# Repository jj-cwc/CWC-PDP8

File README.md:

# CWC-PDP8
PDP-8 implementation on an FPGA

For more information, please see:
- [Cold War Computing website](http://coldwarcomputing.com)
- [PDP-8 Maintenance Manual, Vol. 1](http://vandermark.ch/pdp8/uploads/PDP8/PDP8.Manuals/DEC-8E-HR1C-D.pdf)
- [PDP-8 Maintenance Manual, Vol. 2](http://vandermark.ch/pdp8/uploads/PDP8/PDP8.Manuals/DEC-8E-HR2C-D.pdf)
- [PDP-8 Maintenance Manual, Vol. 3](http://vandermark.ch/pdp8/uploads/PDP8/PDP8.Manuals/DEC-8E-HMM3-D.pdf)

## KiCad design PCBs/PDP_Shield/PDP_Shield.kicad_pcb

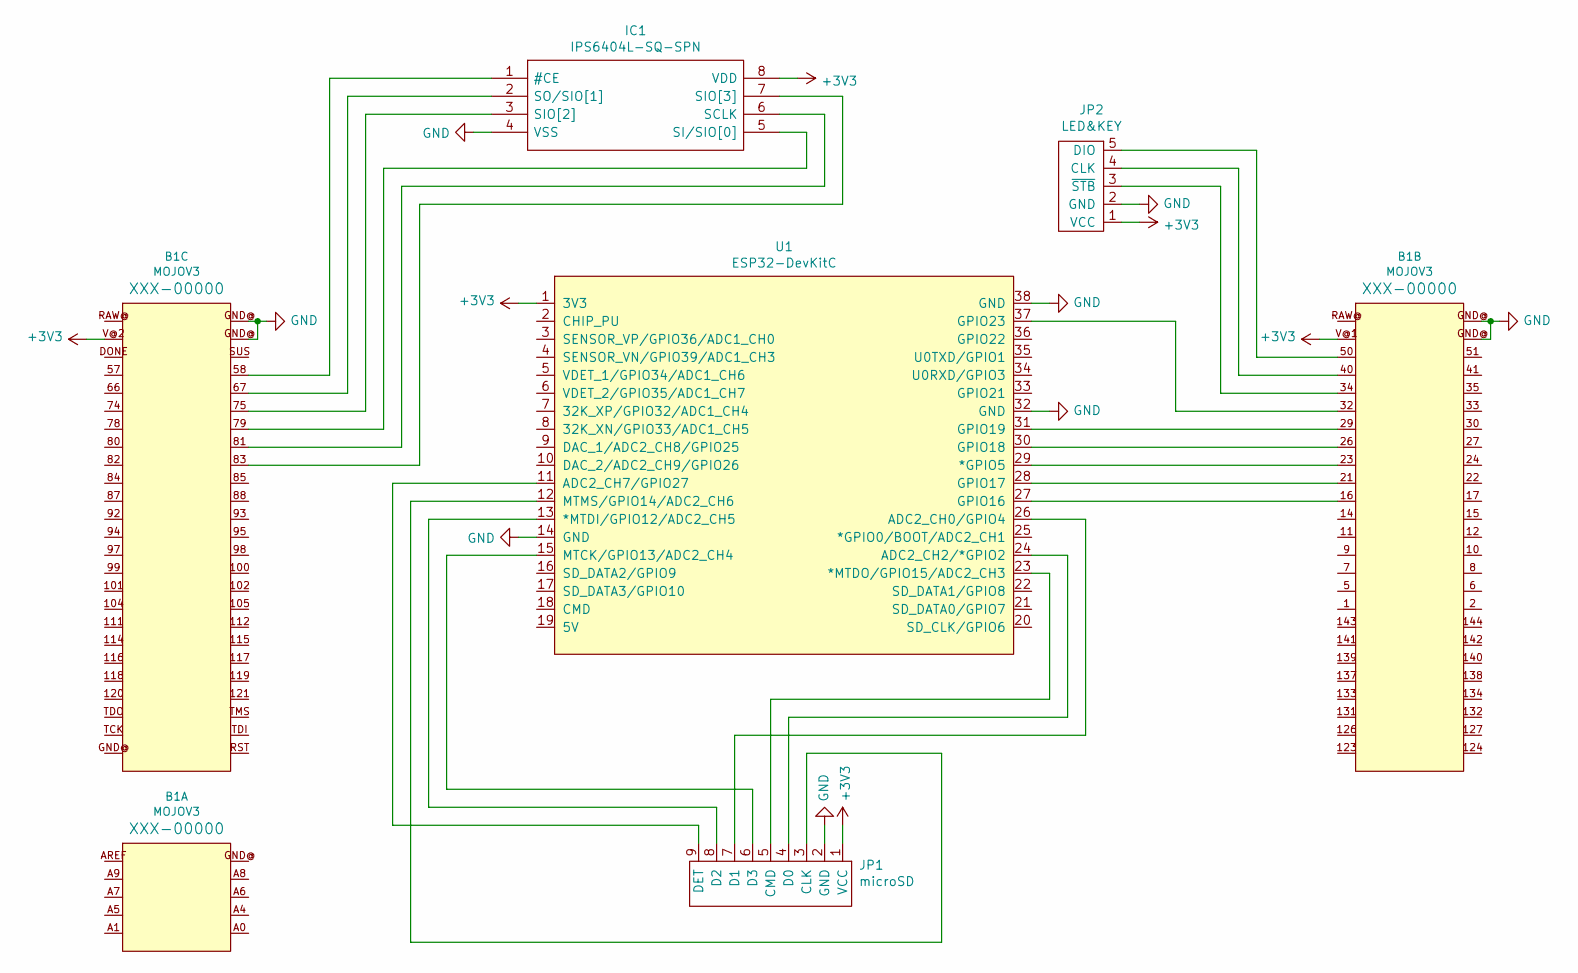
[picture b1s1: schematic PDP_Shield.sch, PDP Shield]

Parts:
B1: MOJOV3; MOJO_V3
IC1: IPS6404L-SQ-SPN; SOIC127P600X175-8N; Manufacturer_Part_Number IPS6404L-SQ-SPN
JP1: microSD; SDIO
JP2: LED&KEY
U1: ESP32-DevKitC

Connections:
+3V3: B1.V@1 (+V), B1.V@2 (+V), IC1.8 (VDD), JP1.1 (VCC), JP2.1 (VCC), U1.1 (3V3)
GND: B1.GND@ (GND), IC1.4 (VSS), JP1.2 (GND), JP2.2 (GND), U1.14 (GND), U1.32 (GND), U1.38 (GND)
unnamed: B1.16, U1.27 (GPIO16)
unnamed: B1.21, U1.28 (GPIO17)
unnamed: B1.23, U1.29 (*GPIO5)
unnamed: B1.26, U1.30 (GPIO18)
unnamed: B1.29, U1.31 (GPIO19)
unnamed: B1.32, U1.37 (GPIO23)
unnamed: B1.34, JP2.3 (~STB)
unnamed: B1.40, JP2.4 (CLK)
unnamed: B1.50, JP2.5 (DIO)
unnamed: B1.58, IC1.1 (#CE)
unnamed: B1.67, IC1.2 (SO/SIO[1])
unnamed: B1.75, IC1.3 (SIO[2])
unnamed: B1.79, IC1.5 (SI/SIO[0])
unnamed: B1.81, IC1.6 (SCLK)
unnamed: B1.83, IC1.7 (SIO[3])
unnamed: JP1.3 (CLK), U1.12 (MTMS/GPIO14/ADC2_CH6)
unnamed: JP1.4 (D0), U1.24 (ADC2_CH2/*GPIO2)
unnamed: JP1.5 (CMD), U1.23 (*MTDO/GPIO15/ADC2_CH3)
unnamed: JP1.6 (D3), U1.15 (MTCK/GPIO13/ADC2_CH4)
unnamed: JP1.7 (D1), U1.26 (ADC2_CH0/GPIO4)
unnamed: JP1.8 (D2), U1.13 (*MTDI/GPIO12/ADC2_CH5)
unnamed: JP1.9 (DET), U1.11 (ADC2_CH7/GPIO27)

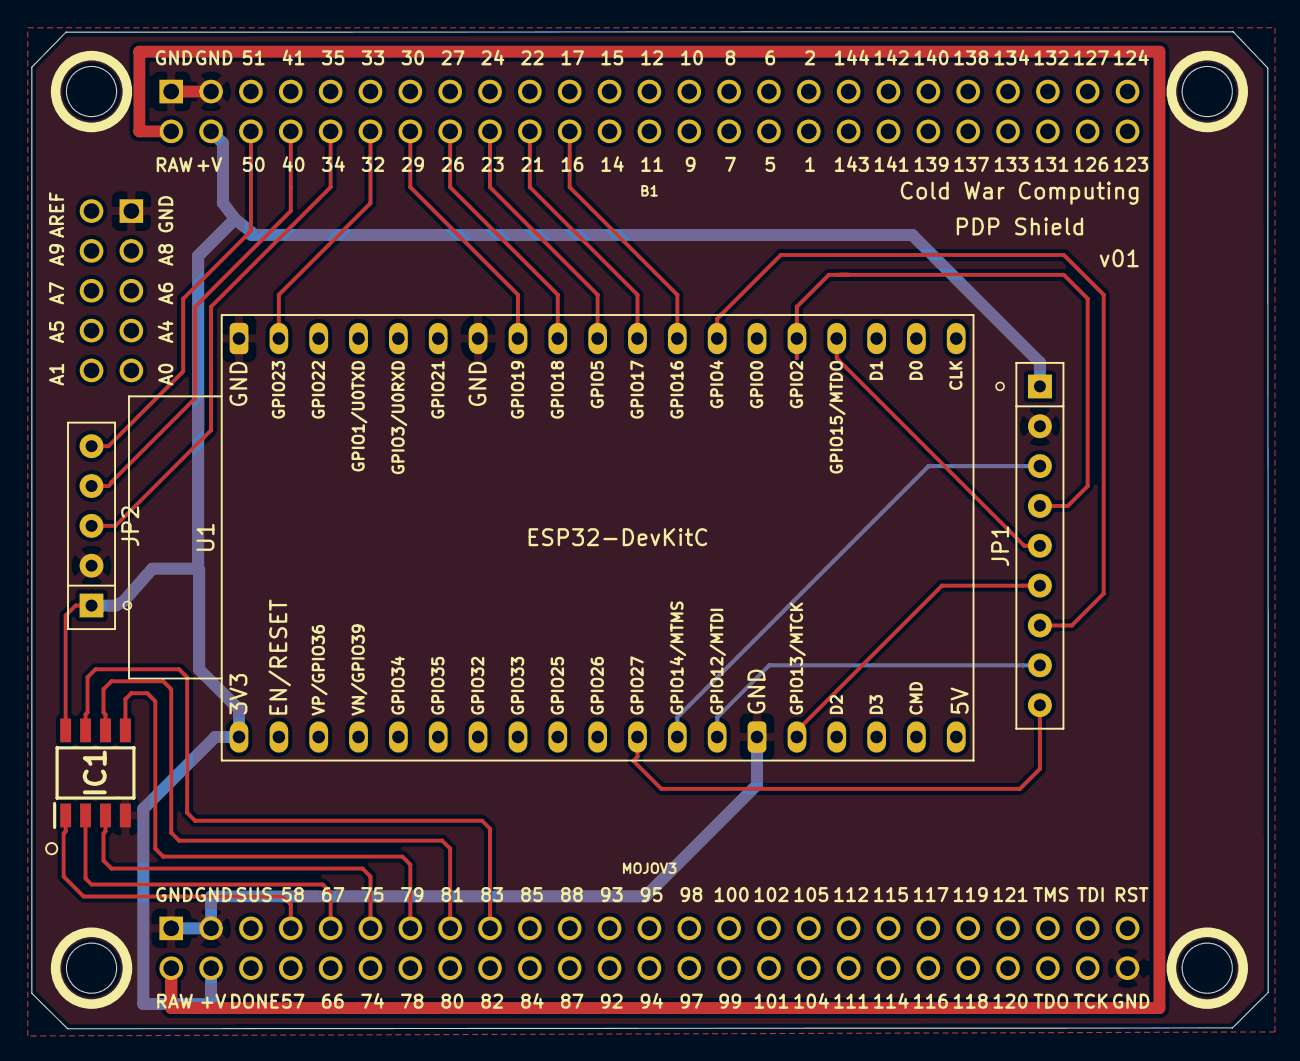
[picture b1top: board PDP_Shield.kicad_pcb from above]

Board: 2 copper layers, 78.8 x 63.6 mm, 5 parts (0 on the bottom side), 24 nets.

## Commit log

2021-10-20 Timing Generator
2021-10-20 changed name of constraints file
2021-10-20 Update README.md
    Added links to more information
2021-10-20 gave clocks more descriptive names
2021-10-20 removed errors
2022-06-24 Added multi_shifter module
2022-06-24 Initial
2022-06-24 Pulled in support files from PDP8 project
2022-07-05 Working on memory access
